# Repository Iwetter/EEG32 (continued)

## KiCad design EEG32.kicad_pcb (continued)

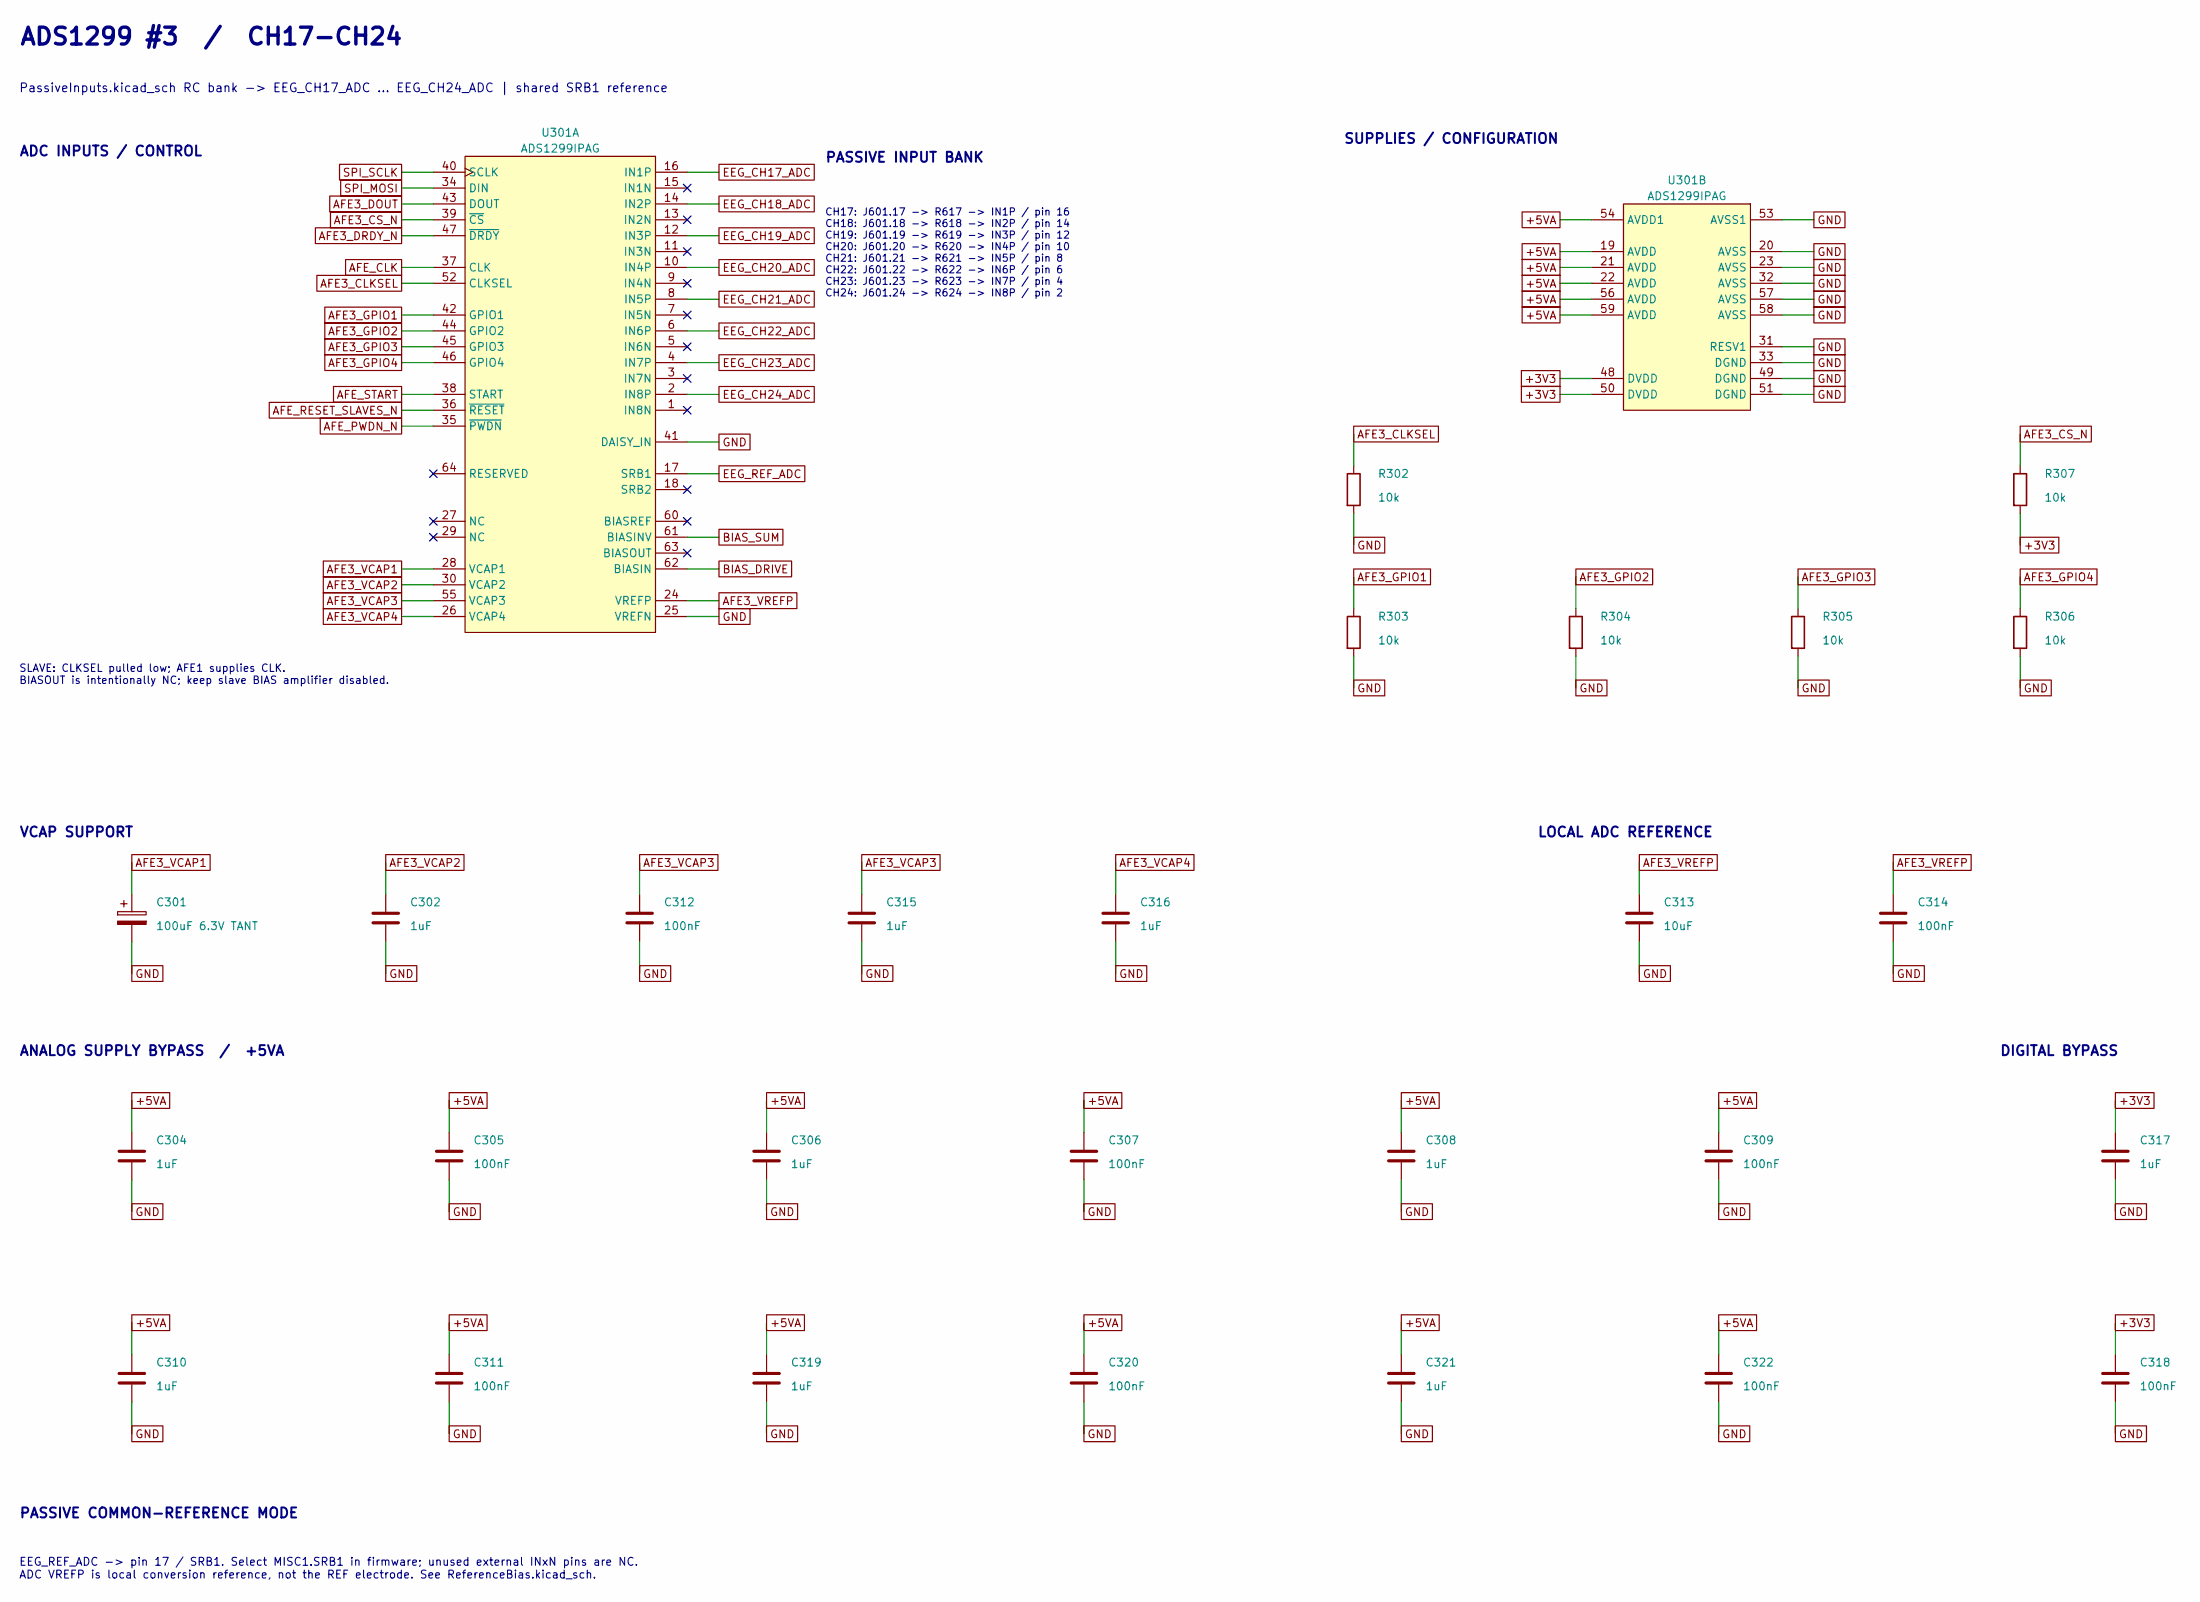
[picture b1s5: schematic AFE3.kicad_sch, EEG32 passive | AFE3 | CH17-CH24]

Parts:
C301: 100uF 6.3V TANT; CP_EIA-3528-21_Kemet-B; MPN T491B107K006AT
C302, C304, C306, C308, C310, C315, C316, C317, C319, C321: 1uF; C0402; MPN GRM155R61A105KE15D
C305, C307, C309, C311, C312, C314, C318, C320, C322: 100nF; C0402; MPN GRM155R71C104KA88D
C313: 10uF; C0603; MPN GRM188R61A106KE69D
R302, R303, R304, R305, R306, R307: 10k; R0402; MPN RC0402FR-0710KL
U301: ADS1299IPAG; PAG0064A_L; MPN ADS1299IPAG

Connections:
+3V3: C317.2, C318.1, R307.2, U301.48 (DVDD), U301.50 (DVDD); also elsewhere on the board
+5VA: C304.1, C305.2, C306.1, C307.2, C308.1, C309.2, C310.1, C311.2, C319.1, C320.1, C321.1, C322.1, U301.19 (AVDD), U301.21 (AVDD), U301.22 (AVDD), U301.54 (AVDD1), U301.56 (AVDD), U301.59 (AVDD); also elsewhere on the board
AFE3_CLKSEL: R302.1, U301.52 (CLKSEL)
AFE3_CS_N: R307.1, U301.39 (~CS); also elsewhere on the board
AFE3_DOUT: U301.43 (DOUT); also elsewhere on the board
AFE3_DRDY_N: U301.47 (~DRDY); also elsewhere on the board
AFE3_GPIO1: R303.1, U301.42 (GPIO1)
AFE3_GPIO2: R304.1, U301.44 (GPIO2)
AFE3_GPIO3: R305.1, U301.45 (GPIO3)
AFE3_GPIO4: R306.1, U301.46 (GPIO4)
AFE3_VCAP1: C301.1, U301.28 (VCAP1)
AFE3_VCAP2: C302.2, U301.30 (VCAP2)
AFE3_VCAP3: C312.2, C315.2, U301.55 (VCAP3)
AFE3_VCAP4: C316.2, U301.26 (VCAP4)
AFE3_VREFP: C313.1, C314.1, U301.24 (VREFP)
AFE_CLK: U301.37 (CLK); also elsewhere on the board
AFE_PWDN_N: U301.35 (~PWDN); also elsewhere on the board
AFE_RESET_SLAVES_N: U301.36 (~RESET); also elsewhere on the board
AFE_START: U301.38 (START); also elsewhere on the board
BIAS_DRIVE: U301.62 (BIASIN); also elsewhere on the board
BIAS_SUM: U301.61 (BIASINV); also elsewhere on the board
EEG_CH17_ADC: U301.16 (IN1P); also elsewhere on the board
EEG_CH18_ADC: U301.14 (IN2P); also elsewhere on the board
EEG_CH19_ADC: U301.12 (IN3P); also elsewhere on the board
EEG_CH20_ADC: U301.10 (IN4P); also elsewhere on the board
EEG_CH21_ADC: U301.8 (IN5P); also elsewhere on the board
EEG_CH22_ADC: U301.6 (IN6P); also elsewhere on the board
EEG_CH23_ADC: U301.4 (IN7P); also elsewhere on the board
EEG_CH24_ADC: U301.2 (IN8P); also elsewhere on the board
EEG_REF_ADC: U301.17 (SRB1); also elsewhere on the board
GND: C301.2, C302.1, C304.2, C305.1, C306.2, C307.1, C308.2, C309.1, C310.2, C311.1, C312.1, C313.2, C314.2, C315.1, C316.1, C317.1, C318.2, C319.2, C320.2, C321.2, C322.2, R302.2, R303.2, R304.2, R305.2, R306.2, U301.20 (AVSS), U301.23 (AVSS), U301.25 (VREFN), U301.31 (RESV1), U301.32 (AVSS), U301.33 (DGND), U301.41 (DAISY_IN), U301.49 (DGND), U301.51 (DGND), U301.53 (AVSS1), U301.57 (AVSS), U301.58 (AVSS); also elsewhere on the board
SPI_MOSI: U301.34 (DIN); also elsewhere on the board
SPI_SCLK: U301.40 (SCLK); also elsewhere on the board

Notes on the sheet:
ADS1299 #3 / CH17-CH24
PassiveInputs.kicad_sch RC bank -> EEG_CH17_ADC ... EEG_CH24_ADC | shared SRB1 reference
ADC INPUTS / CONTROL
SUPPLIES / CONFIGURATION
VCAP SUPPORT
LOCAL ADC REFERENCE
ANALOG SUPPLY BYPASS / +5VA
DIGITAL BYPASS
PASSIVE COMMON-REFERENCE MODE
EEG_REF_ADC -> pin 17 / SRB1. Select MISC1.SRB1 in firmware; unused external INxN pins are NC. ADC VREFP is local conversion reference, not the REF electrode. See ReferenceBias.kicad_sch.
SLAVE: CLKSEL pulled low; AFE1 supplies CLK. BIASOUT is intentionally NC; keep slave BIAS amplifier disabled.
PASSIVE INPUT BANK
CH17: J601.17 -> R617 -> IN1P / pin 16 CH18: J601.18 -> R618 -> IN2P / pin 14 CH19: J601.19 -> R619 -> IN3P / pin 12 CH20: J601.20 -> R620 -> IN4P / pin 10 CH21: J601.21 -> R621 -> IN5P / pin 8 CH22: J601.22 -> R622 -> IN6P / pin 6 CH23: J601.23 -> R623 -> IN7P / pin 4 CH24: J601.24 -> R624 -> IN8P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

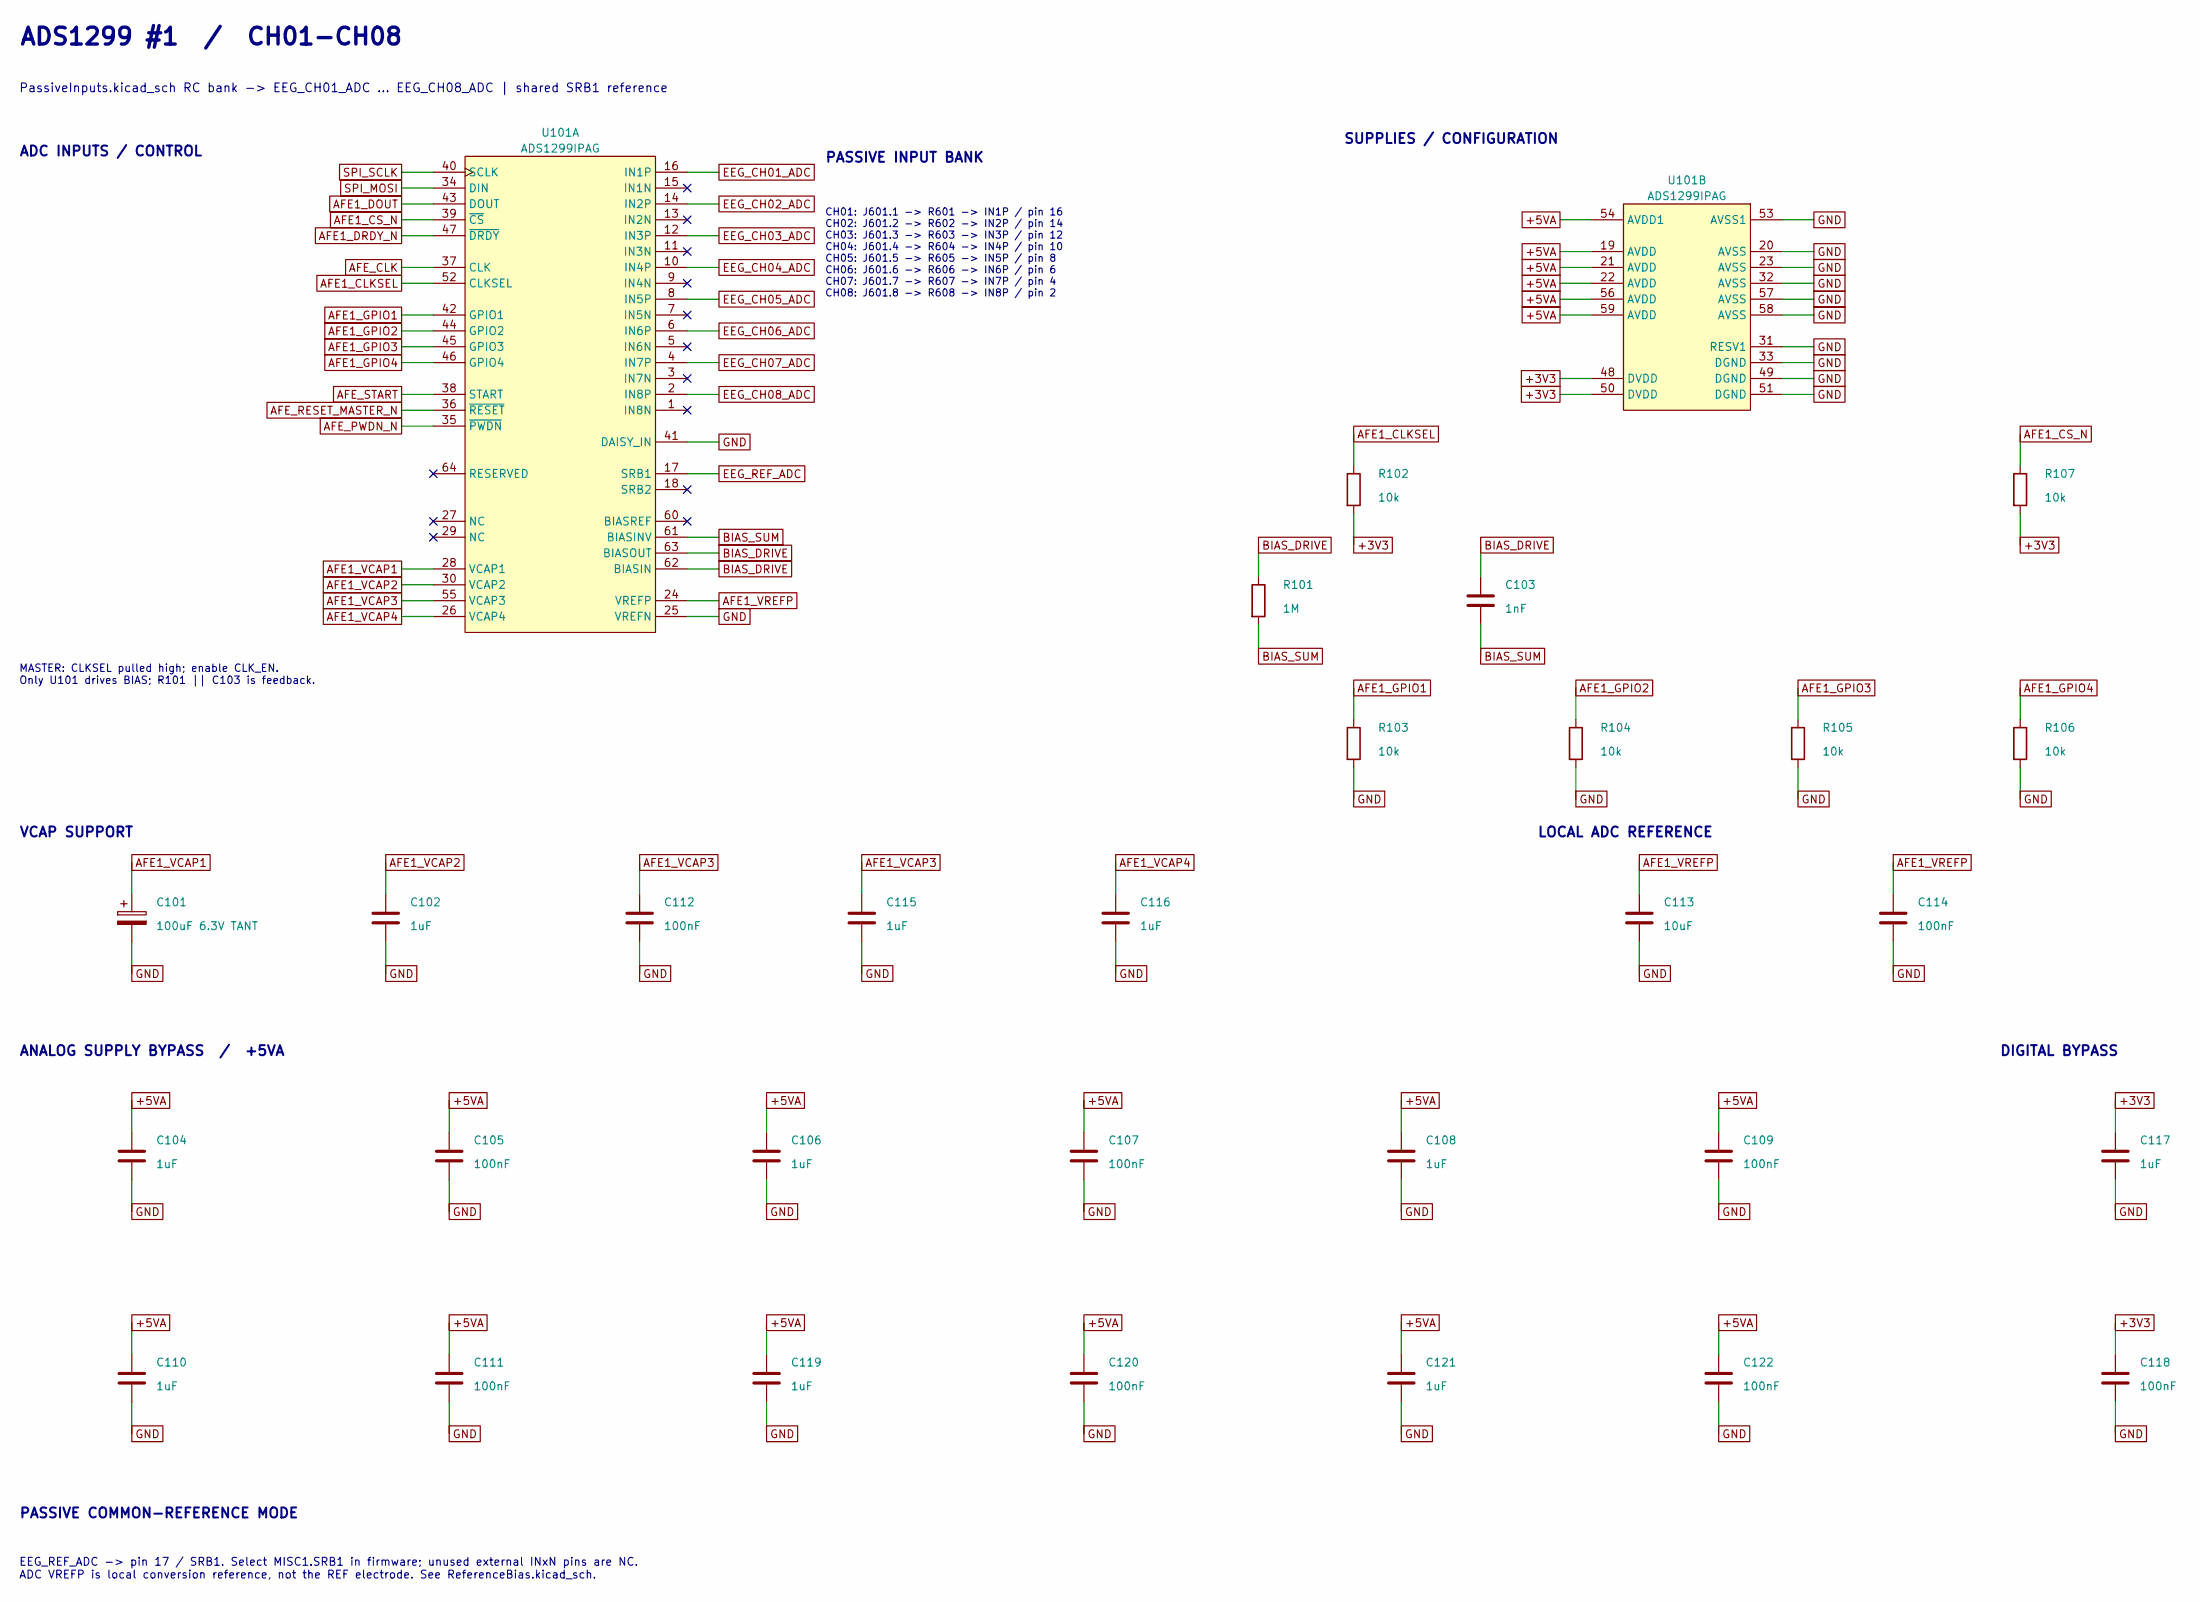
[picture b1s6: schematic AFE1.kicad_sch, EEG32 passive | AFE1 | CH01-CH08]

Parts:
C101: 100uF 6.3V TANT; CP_EIA-3528-21_Kemet-B; MPN T491B107K006AT
C102, C104, C106, C108, C110, C115, C116, C117, C119, C121: 1uF; C0402; MPN GRM155R61A105KE15D
C103: 1nF; C0402; MPN GRM1555C1H102JA01D
C105, C107, C109, C111, C112, C114, C118, C120, C122: 100nF; C0402; MPN GRM155R71C104KA88D
C113: 10uF; C0603; MPN GRM188R61A106KE69D
R101: 1M; R0402; MPN RC0402FR-071ML
R102, R103, R104, R105, R106, R107: 10k; R0402; MPN RC0402FR-0710KL
U101: ADS1299IPAG; PAG0064A_L; MPN ADS1299IPAG

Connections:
+3V3: C117.2, C118.1, R102.2, R107.2, U101.48 (DVDD), U101.50 (DVDD); also elsewhere on the board
+5VA: C104.1, C105.2, C106.1, C107.2, C108.1, C109.2, C110.1, C111.2, C119.1, C120.1, C121.1, C122.1, U101.19 (AVDD), U101.21 (AVDD), U101.22 (AVDD), U101.54 (AVDD1), U101.56 (AVDD), U101.59 (AVDD); also elsewhere on the board
AFE1_CLKSEL: R102.1, U101.52 (CLKSEL)
AFE1_CS_N: R107.1, U101.39 (~CS); also elsewhere on the board
AFE1_DOUT: U101.43 (DOUT); also elsewhere on the board
AFE1_DRDY_N: U101.47 (~DRDY); also elsewhere on the board
AFE1_GPIO1: R103.1, U101.42 (GPIO1)
AFE1_GPIO2: R104.1, U101.44 (GPIO2)
AFE1_GPIO3: R105.1, U101.45 (GPIO3)
AFE1_GPIO4: R106.1, U101.46 (GPIO4)
AFE1_VCAP1: C101.1, U101.28 (VCAP1)
AFE1_VCAP2: C102.2, U101.30 (VCAP2)
AFE1_VCAP3: C112.2, C115.2, U101.55 (VCAP3)
AFE1_VCAP4: C116.2, U101.26 (VCAP4)
AFE1_VREFP: C113.1, C114.1, U101.24 (VREFP)
AFE_CLK: U101.37 (CLK); also elsewhere on the board
AFE_PWDN_N: U101.35 (~PWDN); also elsewhere on the board
AFE_RESET_MASTER_N: U101.36 (~RESET); also elsewhere on the board
AFE_START: U101.38 (START); also elsewhere on the board
BIAS_DRIVE: C103.1, R101.1, U101.62 (BIASIN), U101.63 (BIASOUT); also elsewhere on the board
BIAS_SUM: C103.2, R101.2, U101.61 (BIASINV); also elsewhere on the board
EEG_CH01_ADC: U101.16 (IN1P); also elsewhere on the board
EEG_CH02_ADC: U101.14 (IN2P); also elsewhere on the board
EEG_CH03_ADC: U101.12 (IN3P); also elsewhere on the board
EEG_CH04_ADC: U101.10 (IN4P); also elsewhere on the board
EEG_CH05_ADC: U101.8 (IN5P); also elsewhere on the board
EEG_CH06_ADC: U101.6 (IN6P); also elsewhere on the board
EEG_CH07_ADC: U101.4 (IN7P); also elsewhere on the board
EEG_CH08_ADC: U101.2 (IN8P); also elsewhere on the board
EEG_REF_ADC: U101.17 (SRB1); also elsewhere on the board
GND: C101.2, C102.1, C104.2, C105.1, C106.2, C107.1, C108.2, C109.1, C110.2, C111.1, C112.1, C113.2, C114.2, C115.1, C116.1, C117.1, C118.2, C119.2, C120.2, C121.2, C122.2, R103.2, R104.2, R105.2, R106.2, U101.20 (AVSS), U101.23 (AVSS), U101.25 (VREFN), U101.31 (RESV1), U101.32 (AVSS), U101.33 (DGND), U101.41 (DAISY_IN), U101.49 (DGND), U101.51 (DGND), U101.53 (AVSS1), U101.57 (AVSS), U101.58 (AVSS); also elsewhere on the board
SPI_MOSI: U101.34 (DIN); also elsewhere on the board
SPI_SCLK: U101.40 (SCLK); also elsewhere on the board

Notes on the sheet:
ADS1299 #1 / CH01-CH08
PassiveInputs.kicad_sch RC bank -> EEG_CH01_ADC ... EEG_CH08_ADC | shared SRB1 reference
ADC INPUTS / CONTROL
SUPPLIES / CONFIGURATION
VCAP SUPPORT
LOCAL ADC REFERENCE
ANALOG SUPPLY BYPASS / +5VA
DIGITAL BYPASS
PASSIVE COMMON-REFERENCE MODE
EEG_REF_ADC -> pin 17 / SRB1. Select MISC1.SRB1 in firmware; unused external INxN pins are NC. ADC VREFP is local conversion reference, not the REF electrode. See ReferenceBias.kicad_sch.
MASTER: CLKSEL pulled high; enable CLK_EN. Only U101 drives BIAS; R101 || C103 is feedback.
PASSIVE INPUT BANK
CH01: J601.1 -> R601 -> IN1P / pin 16 CH02: J601.2 -> R602 -> IN2P / pin 14 CH03: J601.3 -> R603 -> IN3P / pin 12 CH04: J601.4 -> R604 -> IN4P / pin 10 CH05: J601.5 -> R605 -> IN5P / pin 8 CH06: J601.6 -> R606 -> IN6P / pin 6 CH07: J601.7 -> R607 -> IN7P / pin 4 CH08: J601.8 -> R608 -> IN8P / pin 2

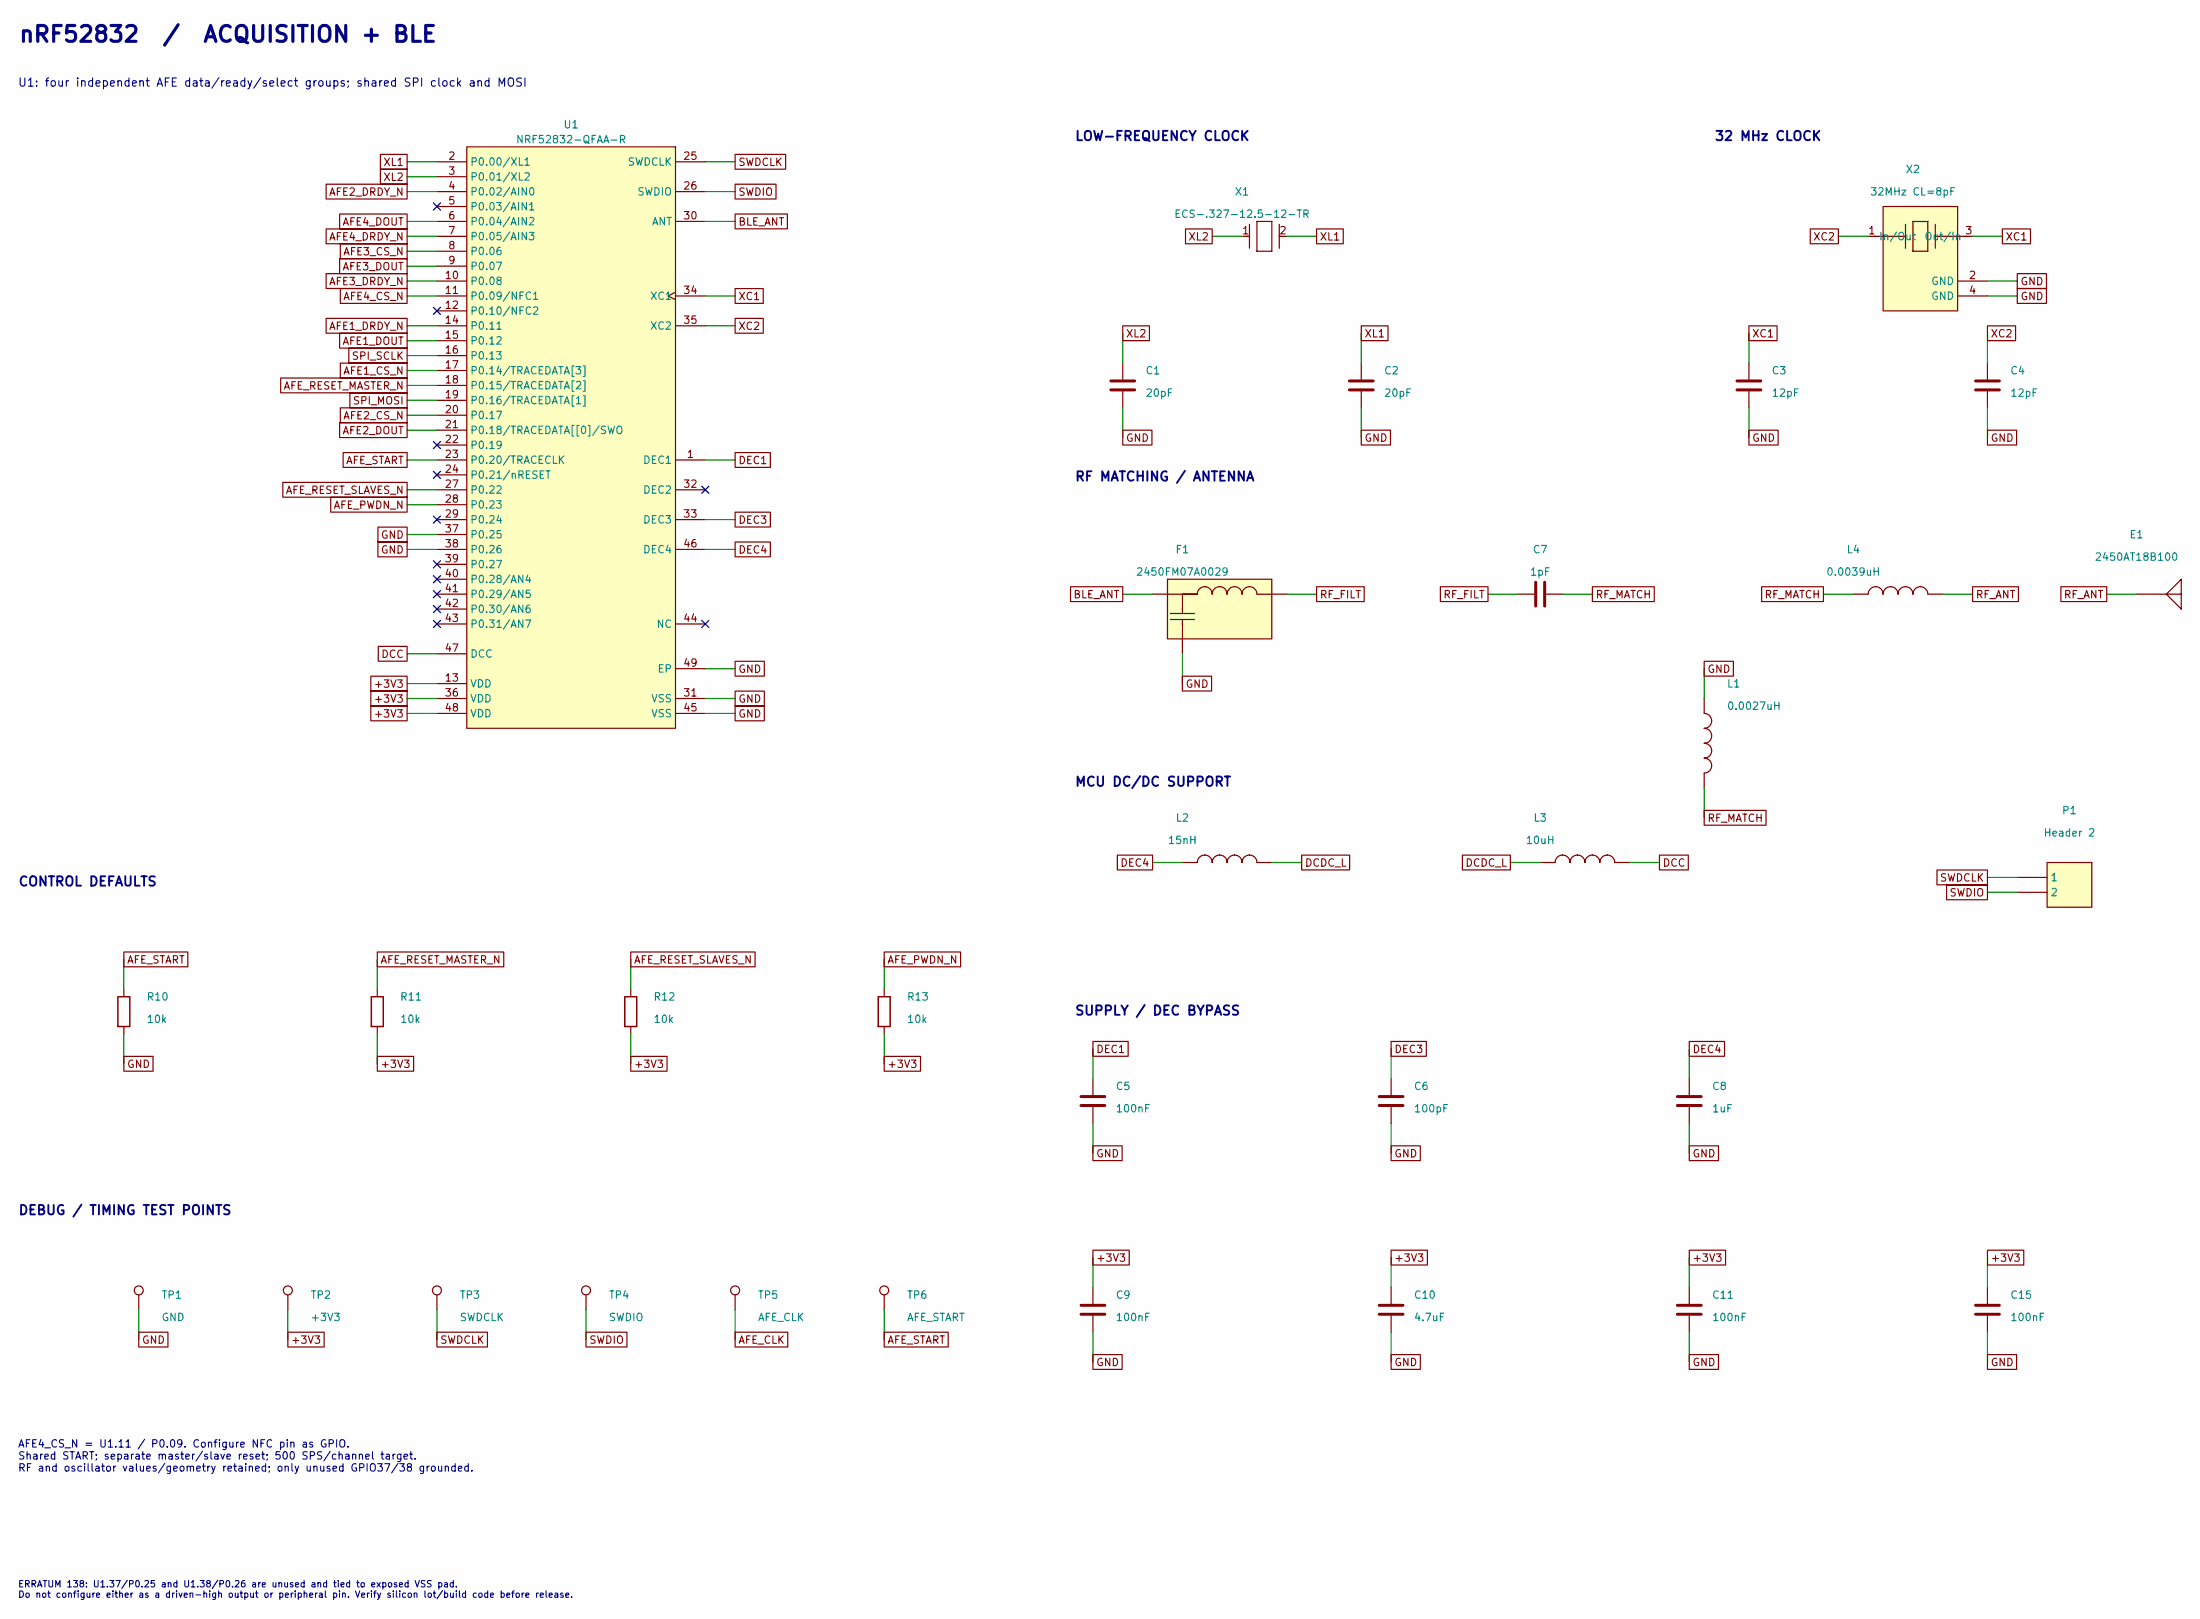
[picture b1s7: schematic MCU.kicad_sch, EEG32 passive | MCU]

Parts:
C1, C2: 20pF; C0402; MPN GJM1555C1H200FB01D
C3, C4: 12pF; C0402; MPN 04025U120FAT2A
C5, C9: 100nF; C0402; MPN MSAST105SB5104KFNA01
C6: 100pF; C0402; MPN CC0402FRNPO9BN101
C7: 1pF; C0402; MPN GCQ1555C1H1R0BB01D
C8: 1uF; C0603; MPN GRM188R61A105KA61D
C10: 4.7uF; C0402; MPN GRM155R60J475ME87D
C11, C15: 100nF; C0402; MPN GRM155R71C104KA88D
E1: 2450AT18B100; MPN 2450AT18B100E
F1: 2450FM07A0029; MPN 2450FM07A0029T
L1: 0.0027uH; L0402; MPN LQW15AN2N7G8ZD
L2: 15nH; L0402; MPN LQG15HS15NJ02D
L3: 10uH; L0603; MPN LQM18DN100M70L
L4: 0.0039uH; L0402; MPN CW100505-3N9J
P1: Header 2; HDR1X2; MPN NOT PURCHASED
R10, R11, R12, R13: 10k; R0402; MPN RC0402FR-0710KL
TP1: GND; TestPoint_Pad_D1.5mm; MPN NOT PURCHASED
TP2: +3V3; TestPoint_Pad_D1.5mm; MPN NOT PURCHASED
TP3: SWDCLK; TestPoint_Pad_D1.5mm; MPN NOT PURCHASED
TP4: SWDIO; TestPoint_Pad_D1.5mm; MPN NOT PURCHASED
TP5: AFE_CLK; TestPoint_Pad_D1.5mm; MPN NOT PURCHASED
TP6: AFE_START; TestPoint_Pad_D1.5mm; MPN NOT PURCHASED
U1: NRF52832-QFAA-R; NRF52832-QFAA-R7; MPN NRF52832-QFAA-R
X1: ECS-.327-12.5-12-TR; FP-ECX-12-MFG; MPN ECS-.327-12.5-12-TR
X2: 32MHz CL=8pF; FP-ECX-1637-MFG; MPN ECS-320-8-37CKM

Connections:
+3V3: C9.1, C10.1, C11.1, C15.1, R11.2, R12.2, R13.2, TP2.1, U1.13 (VDD), U1.36 (VDD), U1.48 (VDD); also elsewhere on the board
AFE1_CS_N: U1.17 (P0.14/TRACEDATA[3]); also elsewhere on the board
AFE1_DOUT: U1.15 (P0.12); also elsewhere on the board
AFE1_DRDY_N: U1.14 (P0.11); also elsewhere on the board
AFE2_CS_N: U1.20 (P0.17); also elsewhere on the board
AFE2_DOUT: U1.21 (P0.18/TRACEDATA[[0]/SWO); also elsewhere on the board
AFE2_DRDY_N: U1.4 (P0.02/AIN0); also elsewhere on the board
AFE3_CS_N: U1.8 (P0.06); also elsewhere on the board
AFE3_DOUT: U1.9 (P0.07); also elsewhere on the board
AFE3_DRDY_N: U1.10 (P0.08); also elsewhere on the board
AFE4_CS_N: U1.11 (P0.09/NFC1); also elsewhere on the board
AFE4_DOUT: U1.6 (P0.04/AIN2); also elsewhere on the board
AFE4_DRDY_N: U1.7 (P0.05/AIN3); also elsewhere on the board
AFE_CLK: TP5.1; also elsewhere on the board
AFE_PWDN_N: R13.1, U1.28 (P0.23); also elsewhere on the board
AFE_RESET_MASTER_N: R11.1, U1.18 (P0.15/TRACEDATA[2]); also elsewhere on the board
AFE_RESET_SLAVES_N: R12.1, U1.27 (P0.22); also elsewhere on the board
AFE_START: R10.1, TP6.1, U1.23 (P0.20/TRACECLK); also elsewhere on the board
BLE_ANT: F1.1, U1.30 (ANT)
DCC: L3.2, U1.47 (DCC)
DCDC_L: L2.2, L3.1
DEC1: C5.1, U1.1 (DEC1)
DEC3: C6.1, U1.33 (DEC3)
DEC4: C8.2, L2.1, U1.46 (DEC4)
GND: C1.1, C2.1, C3.1, C4.1, C5.2, C6.2, C8.1, C9.2, C10.2, C11.2, C15.2, F1.3, L1.1, R10.2, TP1.1, U1.31 (VSS), U1.37 (P0.25), U1.38 (P0.26), U1.45 (VSS), U1.49 (EP), X2.2 (GND), X2.4 (GND); also elsewhere on the board
RF_ANT: E1.1, L4.2
RF_FILT: C7.1, F1.2
RF_MATCH: C7.2, L1.2, L4.1
SPI_MOSI: U1.19 (P0.16/TRACEDATA[1]); also elsewhere on the board
SPI_SCLK: U1.16 (P0.13); also elsewhere on the board
SWDCLK: P1.1, TP3.1, U1.25 (SWDCLK)
SWDIO: P1.2, TP4.1, U1.26 (SWDIO)
XC1: C3.2, U1.34 (XC1), X2.3 (Out/In)
XC2: C4.2, U1.35 (XC2), X2.1 (In/Out)
XL1: C2.2, U1.2 (P0.00/XL1), X1.2 (Out/In)
XL2: C1.2, U1.3 (P0.01/XL2), X1.1 (In/Out)

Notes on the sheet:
nRF52832 / ACQUISITION + BLE
U1: four independent AFE data/ready/select groups; shared SPI clock and MOSI
LOW-FREQUENCY CLOCK
32 MHz CLOCK
RF MATCHING / ANTENNA
MCU DC/DC SUPPORT
SUPPLY / DEC BYPASS
CONTROL DEFAULTS
DEBUG / TIMING TEST POINTS
AFE4_CS_N = U1.11 / P0.09. Configure NFC pin as GPIO. Shared START; separate master/slave reset; 500 SPS/channel target. RF and oscillator values/geometry retained; only unused GPIO37/38 grounded.
ERRATUM 138: U1.37/P0.25 and U1.38/P0.26 are unused and tied to exposed VSS pad. Do not configure either as a driven-high output or peripheral pin. Verify silicon lot/build code before release.
